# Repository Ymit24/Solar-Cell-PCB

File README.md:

# Solar Cell PCB
For my ELEN433 - Optoelectronics class I created a simple PCB to house a solar cell and provide easy breakout terminals and common functionality. 
This will be used in a lab setting for students to easily interface with the solar cell.
This is also a project for earning honors credit for this course.

# Rendered View

# Report
Along with the completed PCB, this project involves writing a short report which describes the design process, manufacturing and ordering process, assembly process, and a how-to-use guide for future reference.

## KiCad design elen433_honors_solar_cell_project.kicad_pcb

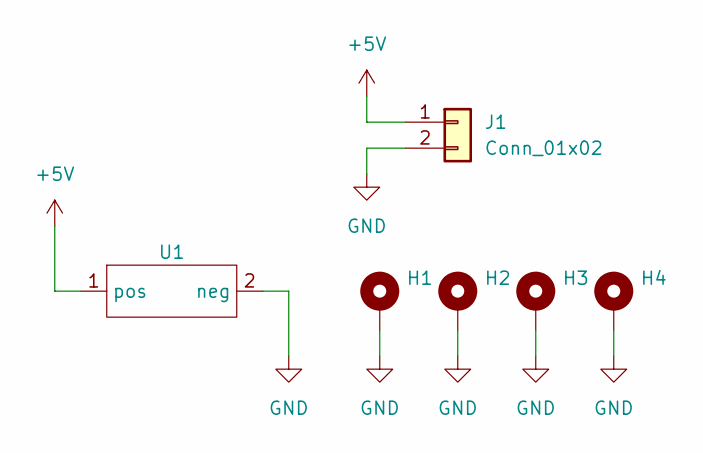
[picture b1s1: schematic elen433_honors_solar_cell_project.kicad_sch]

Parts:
H1, H2, H3, H4: MountingHole_Pad; MountingHole_2.2mm_M2_Pad
J1: Conn_01x02; PinHeader_1x02_P2.54mm_Vertical
U1: Solar

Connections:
+5V: J1.1, U1.1 (pos)
GND: H1.1, H2.1, H3.1, H4.1, J1.2, U1.2 (neg)

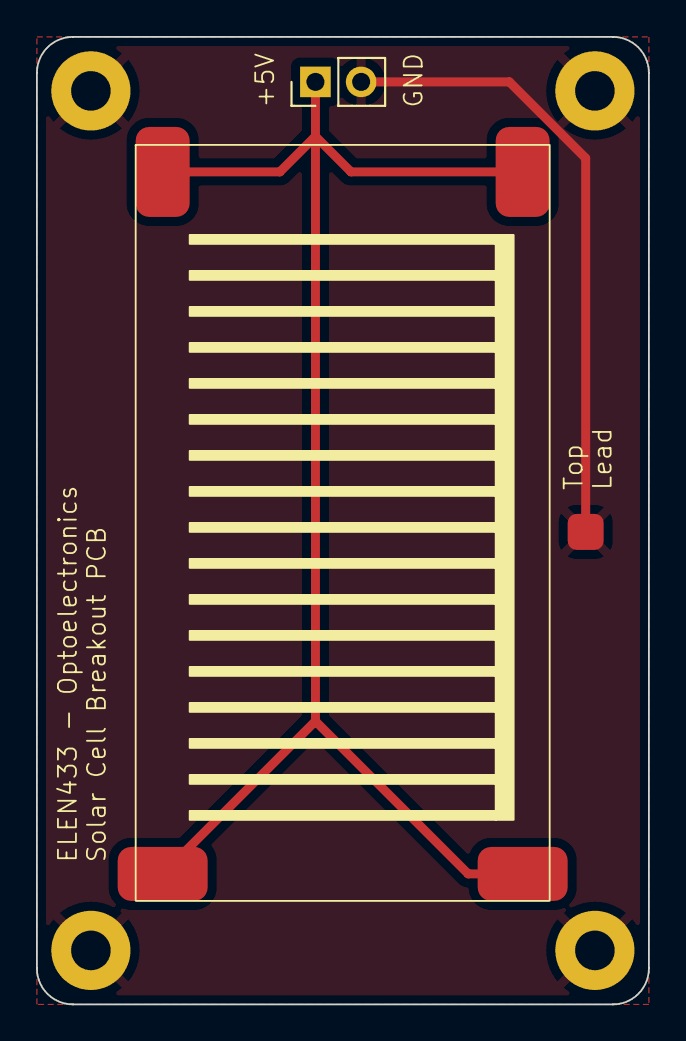
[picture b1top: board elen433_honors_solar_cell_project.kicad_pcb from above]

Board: 2 copper layers, 34.0 x 53.8 mm, 6 parts (0 on the bottom side), 2 nets.

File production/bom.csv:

Designator,Footprint,Quantity,Value,LCSC Part #
"H1, H2, H3, H4",MountingHole_2.2mm_M2_Pad,4,MountingHole_Pad,
J1,PinHeader_1x02_P2.54mm_Vertical,1,Conn_01x02,
U1,Solar,1,~,

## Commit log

2024-04-25 Initial blank KiCad Project
2024-04-25 Create README.md
    Add a basic README with basic project information. Subject to change as the project is developed further.
2024-04-25 added symbol, footprint, and basic schem and board layout
2024-05-08 Created board
2024-05-09 completed.
2024-05-10 Production files
2024-06-01 Update README.md
    Added rendered view.
